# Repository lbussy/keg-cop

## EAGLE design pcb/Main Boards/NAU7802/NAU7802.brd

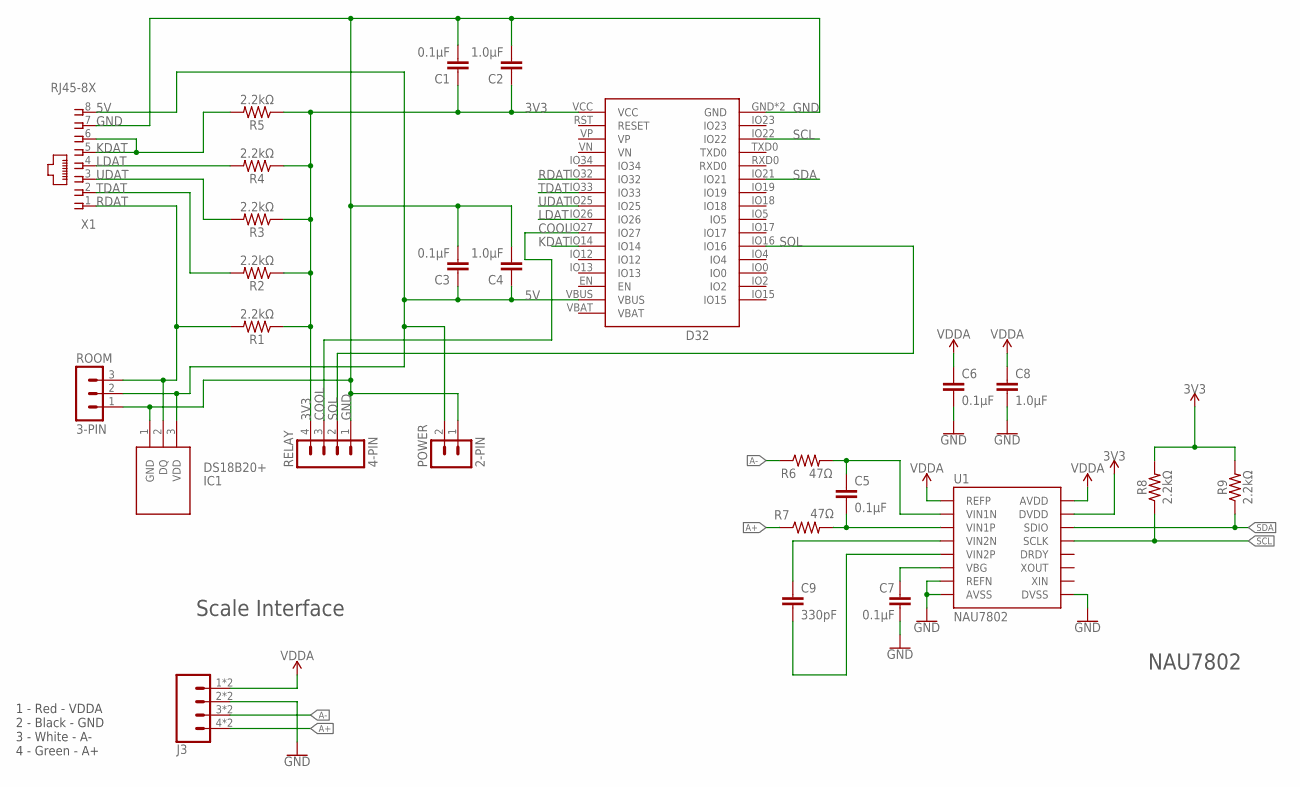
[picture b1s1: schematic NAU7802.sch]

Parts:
C1, C3: 0.1μF; CAP_PTH-2.54
C2, C4: 1.0μF; CAP_PTH-2.54
C5, C6, C7: 0.1μF; C025-024X044
C8: 1.0μF; C025-024X044
C9: 330pF; C025-024X044
D32: Lolin D32; D32_NO_BATT
IC1: DS18B20+; TO-92
J3: Spring Terminal; 1X04_SPRING_TERMINAL
POWER: 2-PIN; HDR-2_VERT
R1, R2, R3, R4, R5, R8, R9: 2.2kΩ; AXIAL-0.3
R6, R7: 47Ω; AXIAL-0.3
RELAY: 4-PIN; MA04-1
ROOM: 3-PIN; HDR-3_VERT
U1: NAU7802; DIP16
X1: RJ45-8X; RJ45-NO-SHIELD

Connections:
3V3: C1.1, C2.1, D32.VCC, R1.P$1 (1), R2.P$1 (1), R3.P$1 (1), R4.P$1 (1), R5.P$1 (1), R8.P$2 (2), R9.P$2 (2), RELAY.4, U1.15 (DVDD)
5V: C3.1, C4.1, D32.VBUS, IC1.3 (VDD), POWER.2, ROOM.2, X1.8
A+: J3.4, J3.8 (4), R7.P$1 (1)
A-: J3.3, J3.7 (3), R6.P$1 (1)
B+: C9.2, U1.5 (VIN2P)
COOL: D32.IO27, RELAY.3
GND: C1.2, C2.2, C3.2, C4.2, C6.2, C7.2, C8.2, D32.GND, D32.GND2 (GND), IC1.1 (GND), J3.2, J3.6 (2), POWER.1, RELAY.1, ROOM.1, U1.7 (REFN), U1.8 (AVSS), U1.9 (DVSS), X1.7
KDAT: D32.IO14, R5.P$2 (2), X1.5, X1.6
LDAT: D32.IO26, R4.P$2 (2), X1.4
unnamed: C9.1, U1.4 (VIN2N)
unnamed: C7.1, U1.6 (VBG)
unnamed: C5.2, R7.P$2 (2), U1.3 (VIN1P)
unnamed: C5.1, R6.P$2 (2), U1.2 (VIN1N)
RDAT: D32.IO32, IC1.2 (DQ), R1.P$2 (2), ROOM.3, X1.1
SCL: D32.IO22, R8.P$1 (1), U1.13 (SCLK)
SDA: D32.IO21, R9.P$1 (1), U1.14 (SDIO)
SOL: D32.IO16, RELAY.2
TDAT: D32.IO33, R2.P$2 (2), X1.2
UDAT: D32.IO25, R3.P$2 (2), X1.3
VDDA: C6.1, C8.1, J3.1, J3.5 (1), U1.1 (REFP), U1.16 (AVDD)

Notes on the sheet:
NAU7802
Scale Interface
1 - Red - VDDA 2 - Black - GND 3 - White - A- 4 - Green - A+

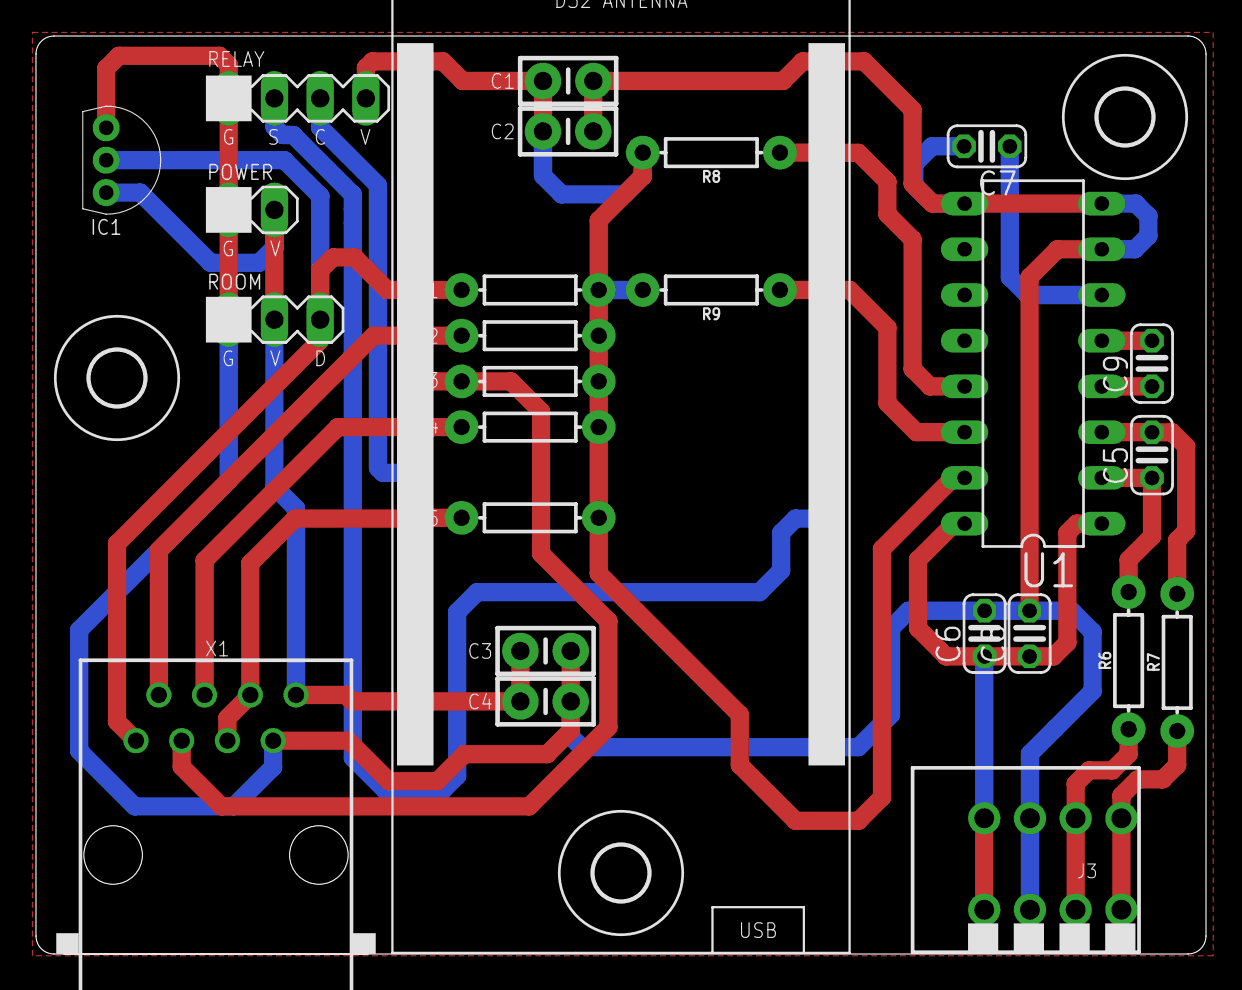
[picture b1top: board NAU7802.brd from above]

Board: 2 copper layers, 65.0 x 51.0 mm, 29 parts (0 on the bottom side), 20 nets.

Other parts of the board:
U$1, U$2, U$3: 3,0

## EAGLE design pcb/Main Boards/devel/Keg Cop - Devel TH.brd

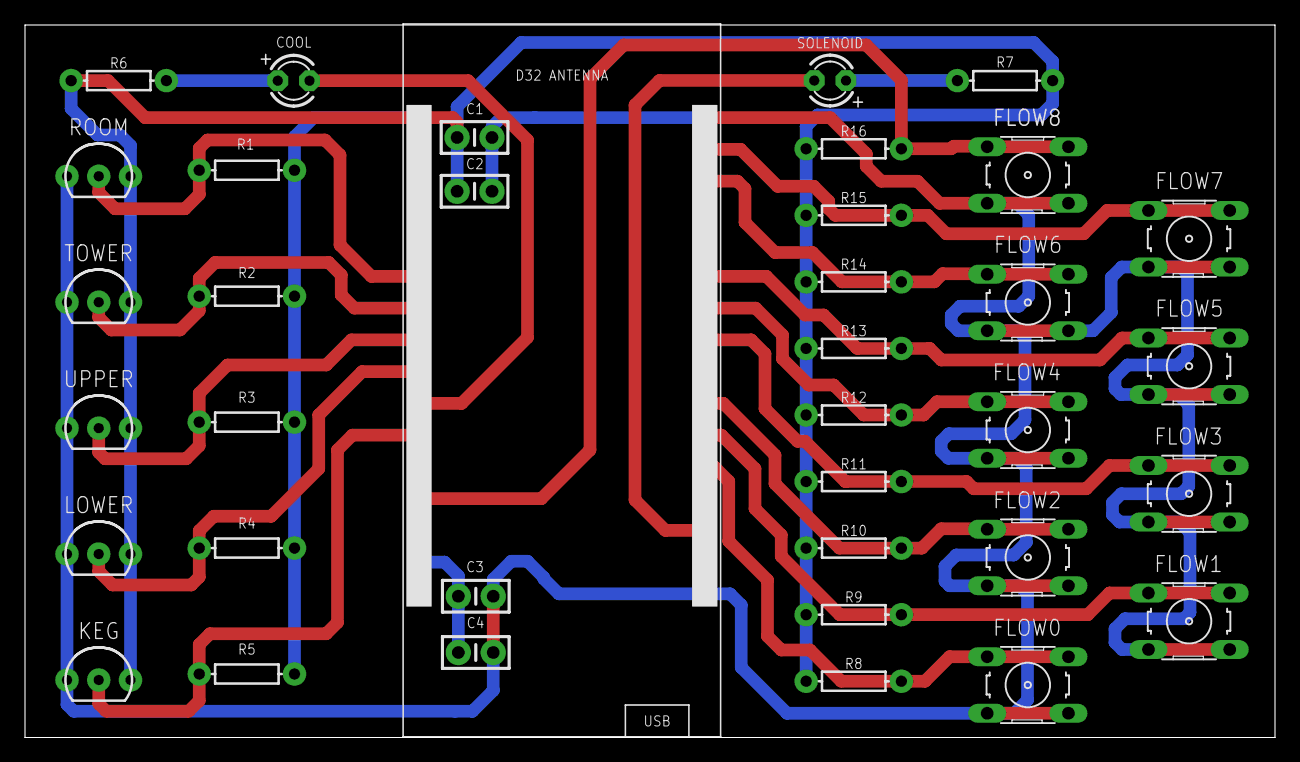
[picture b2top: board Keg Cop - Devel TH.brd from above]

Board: 2 copper layers, 100.0 x 57.0 mm, 37 parts (0 on the bottom side), 21 nets.

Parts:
C1, C3: 0.1μF; CAP_PTH-2.54
C2, C4: 1.0μF; CAP_PTH-2.54
COOL: LED3MM
D32: Lolin D32; D32_NO_BATT
FLOW0, FLOW1, FLOW2, FLOW3, FLOW4, FLOW5, FLOW6, FLOW7, FLOW8: B3F-10XX
KEG: DS18B20; TO-92-AMMO
LOWER: DS18B20; TO-92-AMMO
R1, R2, R3, R4, R5, R8, R9, R10, R11, R12, R13, R14, R15, R16: 2.2kΩ; AXIAL-0.3
R6, R7: 200kΩ; AXIAL-0.3
ROOM: DS18B20; TO-92-AMMO
SOLENOID: LED3MM
TOWER: DS18B20; TO-92-AMMO
UPPER: DS18B20; TO-92-AMMO

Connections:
3V3: C1.1, C2.1, D32.VCC, KEG.3, LOWER.3, R1.P$1, R2.P$1, R3.P$1, R4.P$1, R5.P$1, R6.P$1, R7.P$1, R8.P$1, R9.P$1, R10.P$1, R11.P$1, R12.P$1, R13.P$1, R14.P$1, R15.P$1, R16.P$1, ROOM.3, TOWER.3, UPPER.3
COOL: COOL.K, D32.IO27
FLOW0: D32.IO4, FLOW0.1, FLOW0.2, R8.P$2
FLOW1: D32.IO16, FLOW1.1, FLOW1.2, R9.P$2
FLOW2: D32.IO17, FLOW2.1, FLOW2.2, R10.P$2
FLOW3: D32.IO18, FLOW3.1, FLOW3.2, R11.P$2
FLOW4: D32.IO19, FLOW4.1, FLOW4.2, R12.P$2
FLOW5: D32.IO21, FLOW5.1, FLOW5.2, R13.P$2
FLOW6: D32.IO22, FLOW6.1, FLOW6.2, R14.P$2
FLOW7: D32.IO23, FLOW7.1, FLOW7.2, R15.P$2
FLOW8: D32.IO13, FLOW8.1, FLOW8.2, R16.P$2
GND: C1.2, C2.2, C3.1, C4.1, D32.GND, D32.GND2, FLOW0.3, FLOW0.4, FLOW1.3, FLOW1.4, FLOW2.3, FLOW2.4, FLOW3.3, FLOW3.4, FLOW4.3, FLOW4.4, FLOW5.3, FLOW5.4, FLOW6.3, FLOW6.4, FLOW7.3, FLOW7.4, FLOW8.3, FLOW8.4, KEG.1, LOWER.1, ROOM.1, TOWER.1, UPPER.1
KDAT: D32.IO14, KEG.2, R5.P$2
LDAT: D32.IO26, LOWER.2, R4.P$2
unnamed: COOL.A, R6.P$2
unnamed: R7.P$2, SOLENOID.A
RDAT: D32.IO32, R1.P$2, ROOM.2
SOL: D32.IO2, SOLENOID.K
TDAT: D32.IO33, R2.P$2, TOWER.2
UDAT: D32.IO25, R3.P$2, UPPER.2
VBUS: C3.2, C4.2, D32.VBUS

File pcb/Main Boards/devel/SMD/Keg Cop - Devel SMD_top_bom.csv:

Comment,Designator,Footprint,LCSC Part #
0.1µF,C1 C3,SMD-0805,C28233
1.0µF,C2 C4,SMD-0805,C28323
2k2½,R1 R2 R3 R4 R5 R6 R7 R8 R9 R12 R13 R14 R15 R16,SMD-0805,C17518
60.4½,R10 R11,SMD-0805,C25323
DS18B20Z,KEG LOWER ROOM TOWER UPPER,SOIC127P600X175-8N,C695837
LED_0603LED_SMD_0603,COOL SOLENOID,LED_SMD_0603,C2286
TS08-66-43-BK-160-SMT-67,FLOW0 FLOW1 FLOW2 FLOW3 FLOW4 FLOW5 FLOW6 FLOW7 FLOW8,SW_TS08-66-43-BK-160-SMT-67,C2889023

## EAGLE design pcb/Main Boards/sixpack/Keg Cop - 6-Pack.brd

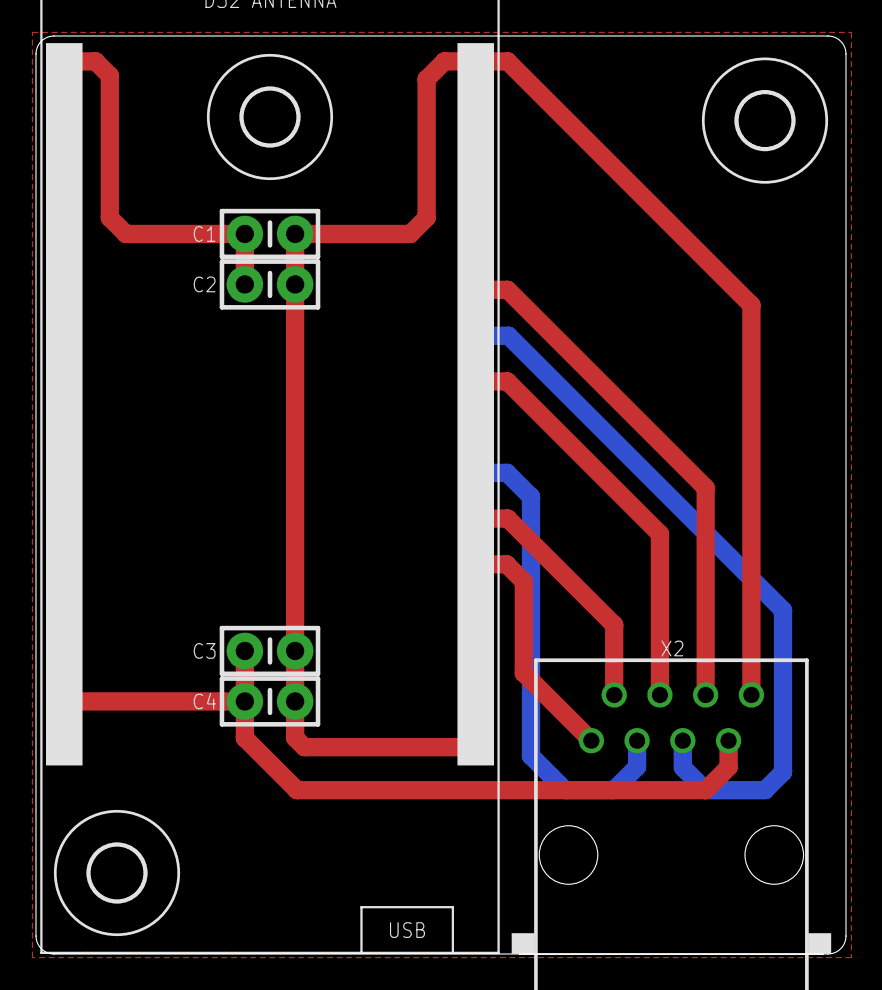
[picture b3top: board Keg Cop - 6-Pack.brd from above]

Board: 2 copper layers, 45.0 x 51.0 mm, 9 parts (0 on the bottom side), 9 nets.

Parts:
C1, C3: 0.1μF; CAP_PTH-2.54
C2, C4: 1.0μF; CAP_PTH-2.54
D32: Lolin D32; D32_NO_BATT
U$1, U$2, U$3: 3,0
X2: RJ45-8X; RJ45-NO-SHIELD

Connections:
5V: C3.1, C4.1, D32.VBUS, X2.7
GND: C1.2, C2.2, C3.2, C4.2, D32.GND, D32.GND2, X2.8
KEG1: D32.IO4, X2.1
KEG2: D32.IO16, X2.2
KEG3: D32.IO17, X2.3
KEG4: D32.IO18, X2.4
KEG5: D32.IO19, X2.5
KEG6: D32.IO21, X2.6
VCC: C1.1, C2.1, D32.VCC

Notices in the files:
parts and their libraries:
SparkFun-Resistors: Licensing: Creative Commons ShareAlike 4.0 International - https://creativecommons.org/licenses/by-sa/4.0
